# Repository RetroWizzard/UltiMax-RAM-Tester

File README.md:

# UltiMax-RAM-Tester
Attention, this is still in development and contains errors.
Do not use this for ordering pcbs.

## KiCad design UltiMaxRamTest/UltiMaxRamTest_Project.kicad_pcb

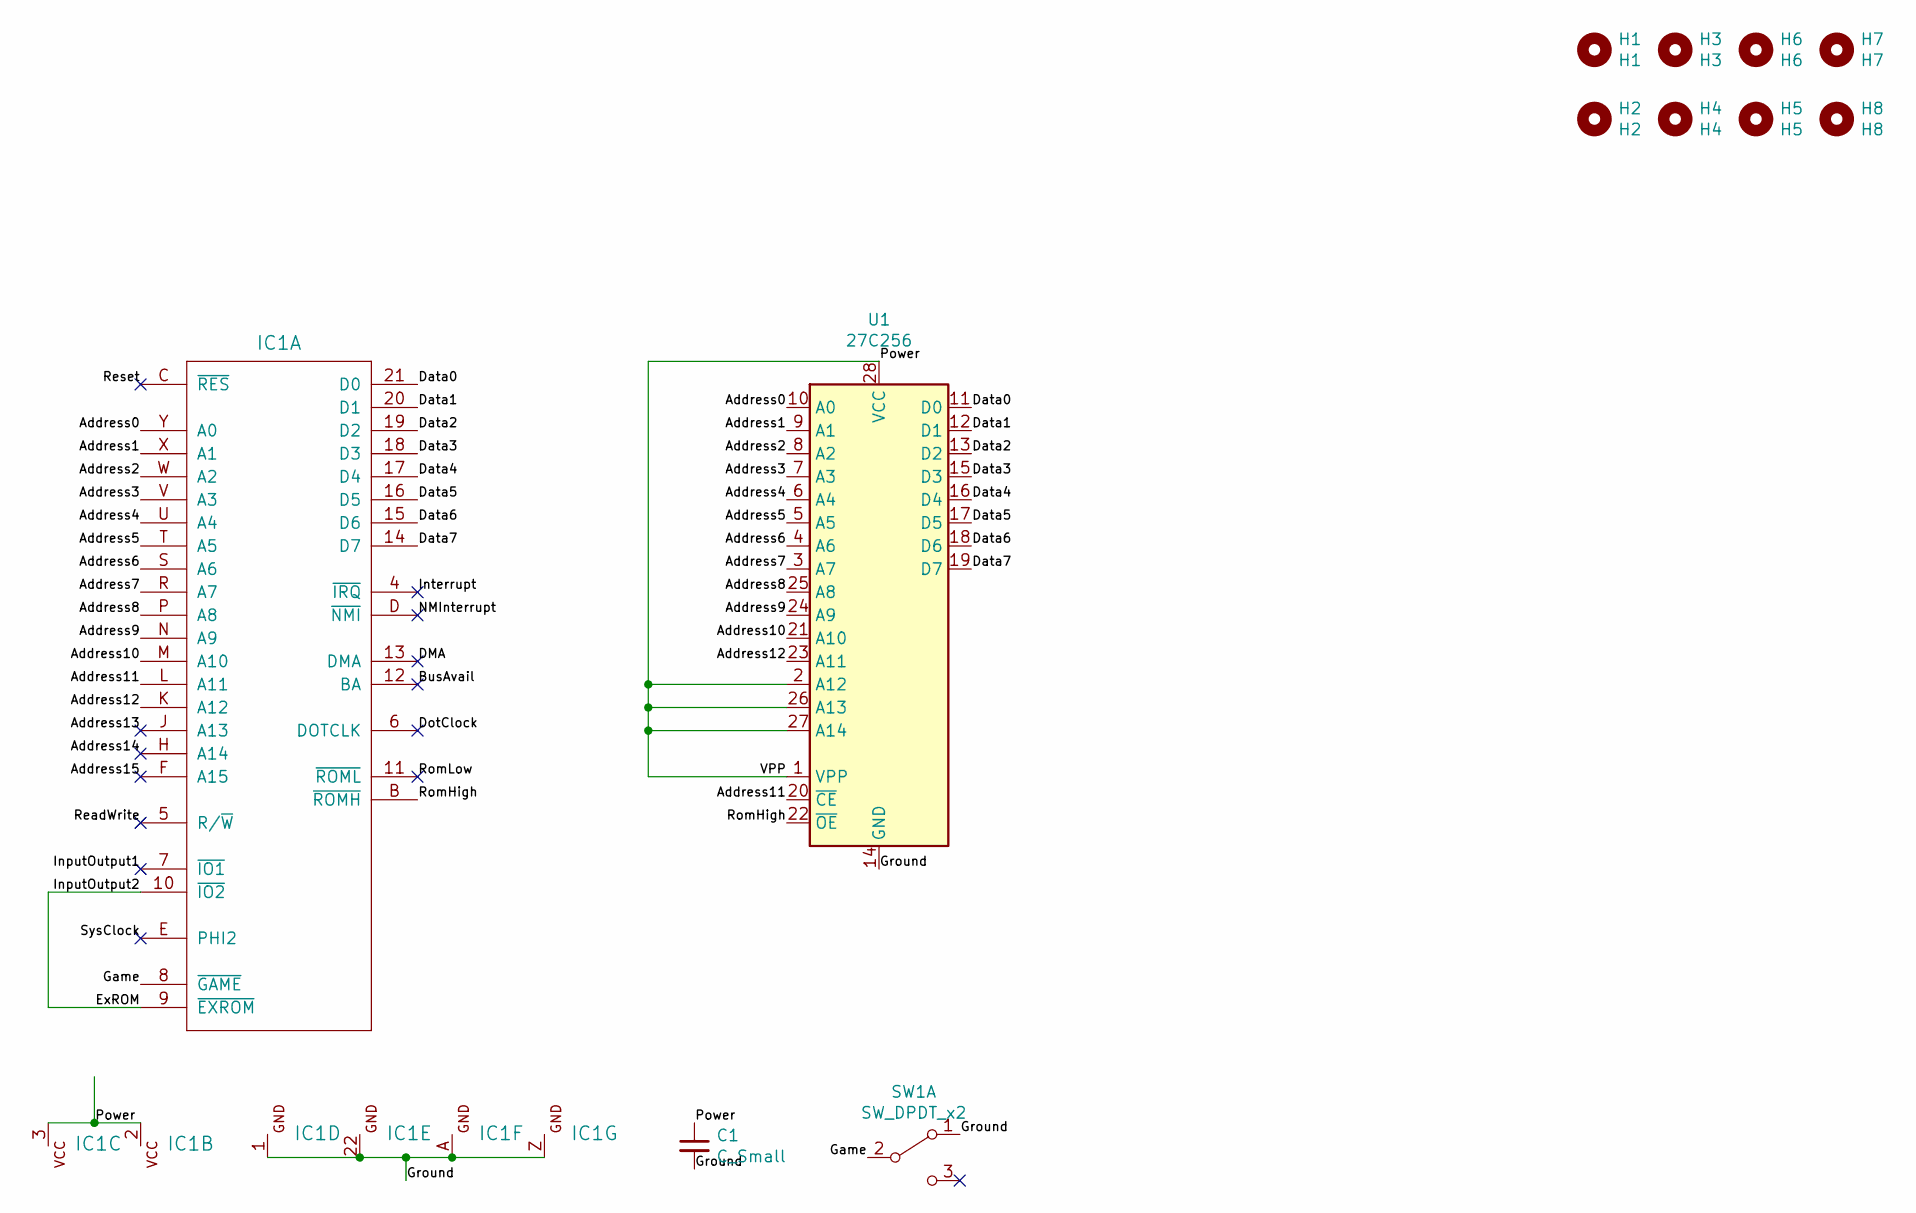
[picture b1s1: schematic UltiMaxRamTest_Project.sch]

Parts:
C1: C_Small; C_Disc_D4.3mm_W1.9mm_P5.00mm
H1: H1; MountingHole_4.5mm_Mod
H2: H2; MountingHole_3.2mm_M3_Mod3
H3: H3; MountingHole_3.2mm_M3_Mod3
H4: H4; MountingHole_4.8mm_Mod
H5: H5; MountingHole_3.2mm_M3_Mod2
H6: H6; MountingHole_3.2mm_M3_Mod2
H7: H7; MountingHole_3.2mm_M3_Mod2
H8: H8; MountingHole_3.2mm_M3_Mod2
IC1: EXPANSION_PORT_C64; C64-Cart_Mod_9mm_Round
SW1: SW_DPDT_x2; SW_E-Switch_MTS-102_SPDT_Angled
U1: 27C256; DIP-28_W15.24mm

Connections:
/Address0: IC1.Y (A0), U1.10 (A0)
/Address1: IC1.X (A1), U1.9 (A1)
/Address2: IC1.W (A2), U1.8 (A2)
/Address3: IC1.V (A3), U1.7 (A3)
/Address4: IC1.U (A4), U1.6 (A4)
/Address5: IC1.T (A5), U1.5 (A5)
/Address6: IC1.S (A6), U1.4 (A6)
/Address7: IC1.R (A7), U1.3 (A7)
/Address8: IC1.P (A8), U1.25 (A8)
/Address9: IC1.N (A9), U1.24 (A9)
/Address10: IC1.M (A10), U1.21 (A10)
/Address11: IC1.L (A11), U1.20 (~CE)
/Address12: IC1.K (A12), U1.23 (A11)
/Address13: IC1.J (A13)
/Address14: IC1.H (A14)
/Address15: IC1.F (A15)
/BusAvail: IC1.12 (BA)
/DMA: IC1.13 (DMA)
/Data0: IC1.21 (D0), U1.11 (D0)
/Data1: IC1.20 (D1), U1.12 (D1)
/Data2: IC1.19 (D2), U1.13 (D2)
/Data3: IC1.18 (D3), U1.15 (D3)
/Data4: IC1.17 (D4), U1.16 (D4)
/Data5: IC1.16 (D5), U1.17 (D5)
/Data6: IC1.15 (D6), U1.18 (D6)
/Data7: IC1.14 (D7), U1.19 (D7)
/DotClock: IC1.6 (DOTCLK)
/ExROM: IC1.9 (~EXROM), IC1.10 (~IO2)
/Game: IC1.8 (~GAME), SW1.2 (B)
/Ground: C1.2, IC1.1 (GND), IC1.22 (GND), IC1.A (GND), IC1.Z (GND), SW1.1 (A), U1.14 (GND)
/InputOutput1: IC1.7 (~IO1)
/Interrupt: IC1.4 (~IRQ)
/NMInterrupt: IC1.D (~NMI)
/Power: C1.1, IC1.2 (VCC), IC1.3 (VCC), U1.1 (VPP), U1.2 (A12), U1.26 (A13), U1.27 (A14), U1.28 (VCC)
/ReadWrite: IC1.5 (R/~W)
/Reset: IC1.C (~RES)
/RomHigh: IC1.B (~ROMH), U1.22 (~OE)
/RomLow: IC1.11 (~ROML)
/SysClock: IC1.E (PHI2)

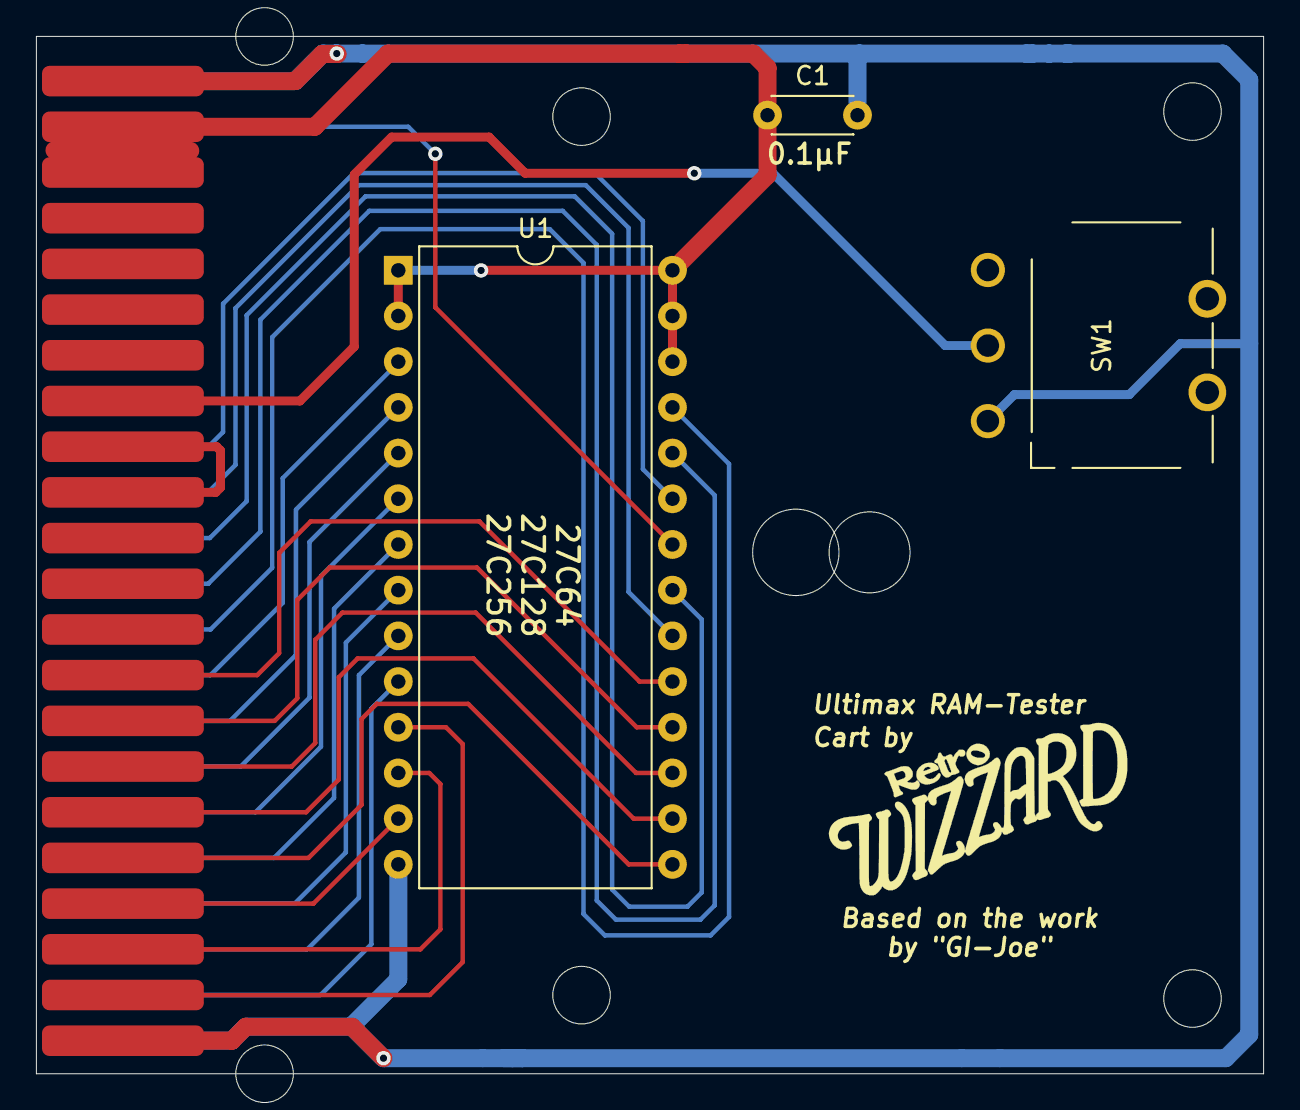
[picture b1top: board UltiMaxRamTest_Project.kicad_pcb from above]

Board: 2 copper layers, 68.2 x 57.7 mm, 12 parts (0 on the bottom side), 26 nets.
